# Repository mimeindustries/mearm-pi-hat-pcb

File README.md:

## MeArm Raspberry Pi HAT PCB

This repository contains the KiCAD project for the MeArm Raspberry Pi HAT

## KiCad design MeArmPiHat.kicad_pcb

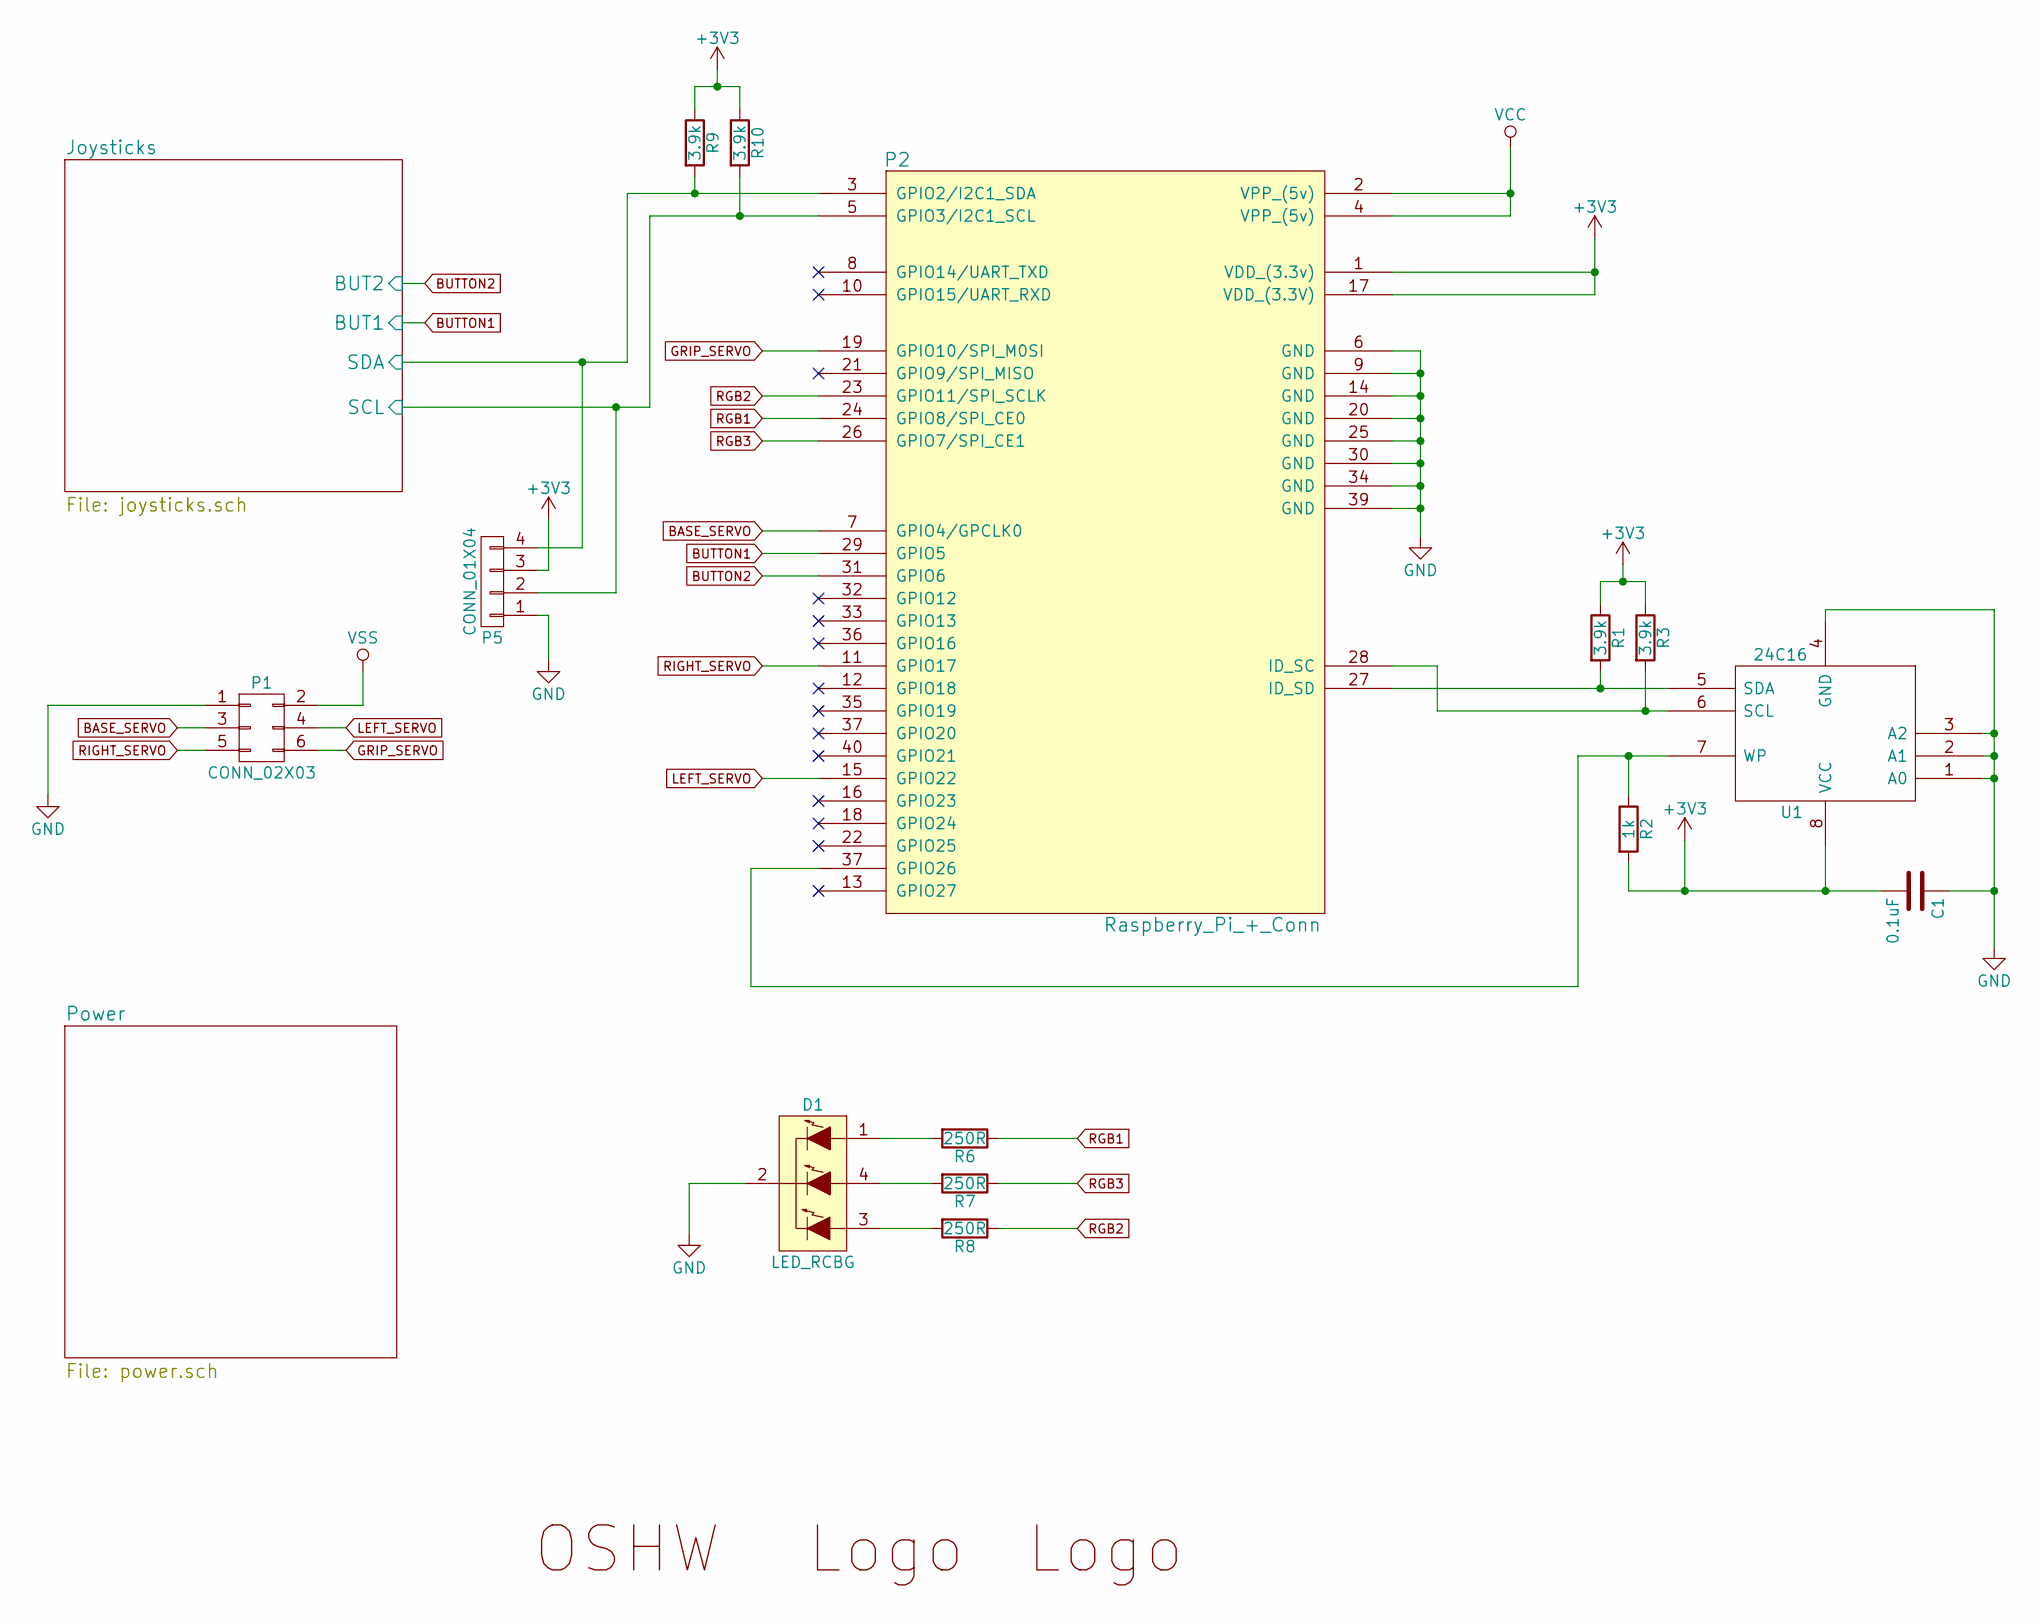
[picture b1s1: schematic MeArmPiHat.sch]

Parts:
ART1: OSHW-LOGO; OSHW_LOGO
ART2: LOGO; MEARM_LOGO_NEW_LARGE
ART3: LOGO; MIME_LOGO
C1: 0.1uF; C_0603
D1: LED_RCBG; LED-RGB-5MM_Common_Cathode
P1: CONN_02X03; Pin_Header_Straight_2x03
P2: Raspberry_Pi_+_Conn; 02x40-SMD-Socket-Flipped; Manfr. Part Number (MFP) REF-182665-01
P5: CONN_01X04; Pin_Header_Angled_1x04
R1, R3, R9, R10: 3.9k; R_0603
R2: 1k; R_0603
R6, R7, R8: 250R; R_0603
U1: 24C16; SOIC-8-N; Manfr. Part Number (MFP) CAT24C32WI

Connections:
+3V3: C1.2, P2.1 (VDD_(3.3v)), P2.17 (VDD_(3.3V)), P5.3, R1.1, R2.2, R3.1, R9.1, R10.1, U1.8 (VCC); also elsewhere on the board
/Joysticks/SCL: P2.5 (GPIO3/I2C1_SCL), P5.2, R10.2; also elsewhere on the board
/Joysticks/SDA: P2.3 (GPIO2/I2C1_SDA), P5.4, R9.2; also elsewhere on the board
BASE_SERVO: P1.3, P2.7 (GPIO4/GPCLK0)
BUTTON1: P2.29 (GPIO5); also elsewhere on the board
BUTTON2: P2.31 (GPIO6); also elsewhere on the board
GND: C1.1, D1.2 (COMMON_CATHODE), P1.1, P2.6 (GND), P2.9 (GND), P2.14 (GND), P2.20 (GND), P2.25 (GND), P2.30 (GND), P2.34 (GND), P2.39 (GND), P5.1, U1.1 (A0), U1.2 (A1), U1.3 (A2), U1.4 (GND); also elsewhere on the board
GRIP_SERVO: P1.6, P2.19 (GPIO10/SPI_M0SI)
LEFT_SERVO: P1.4, P2.15 (GPIO22)
unnamed: D1.1 (RED_ANODE), R6.2
unnamed: D1.3 (BLUE_ANODE), R8.2
unnamed: D1.4 (GREEN_ANODE), R7.2
unnamed: P2.27 (ID_SD), R1.2, U1.5 (SDA)
unnamed: P2.28 (ID_SC), R3.2, U1.6 (SCL)
unnamed: P2.37 (GPIO20), R2.1, U1.7 (WP)
RGB1: P2.24 (GPIO8/SPI_CE0), R6.1
RGB2: P2.23 (GPIO11/SPI_SCLK), R8.1
RGB3: P2.26 (GPIO7/SPI_CE1), R7.1
RIGHT_SERVO: P1.5, P2.11 (GPIO17)
VCC: P2.2 (VPP_(5v)), P2.4 (VPP_(5v)); also elsewhere on the board
VSS: P1.2; also elsewhere on the board

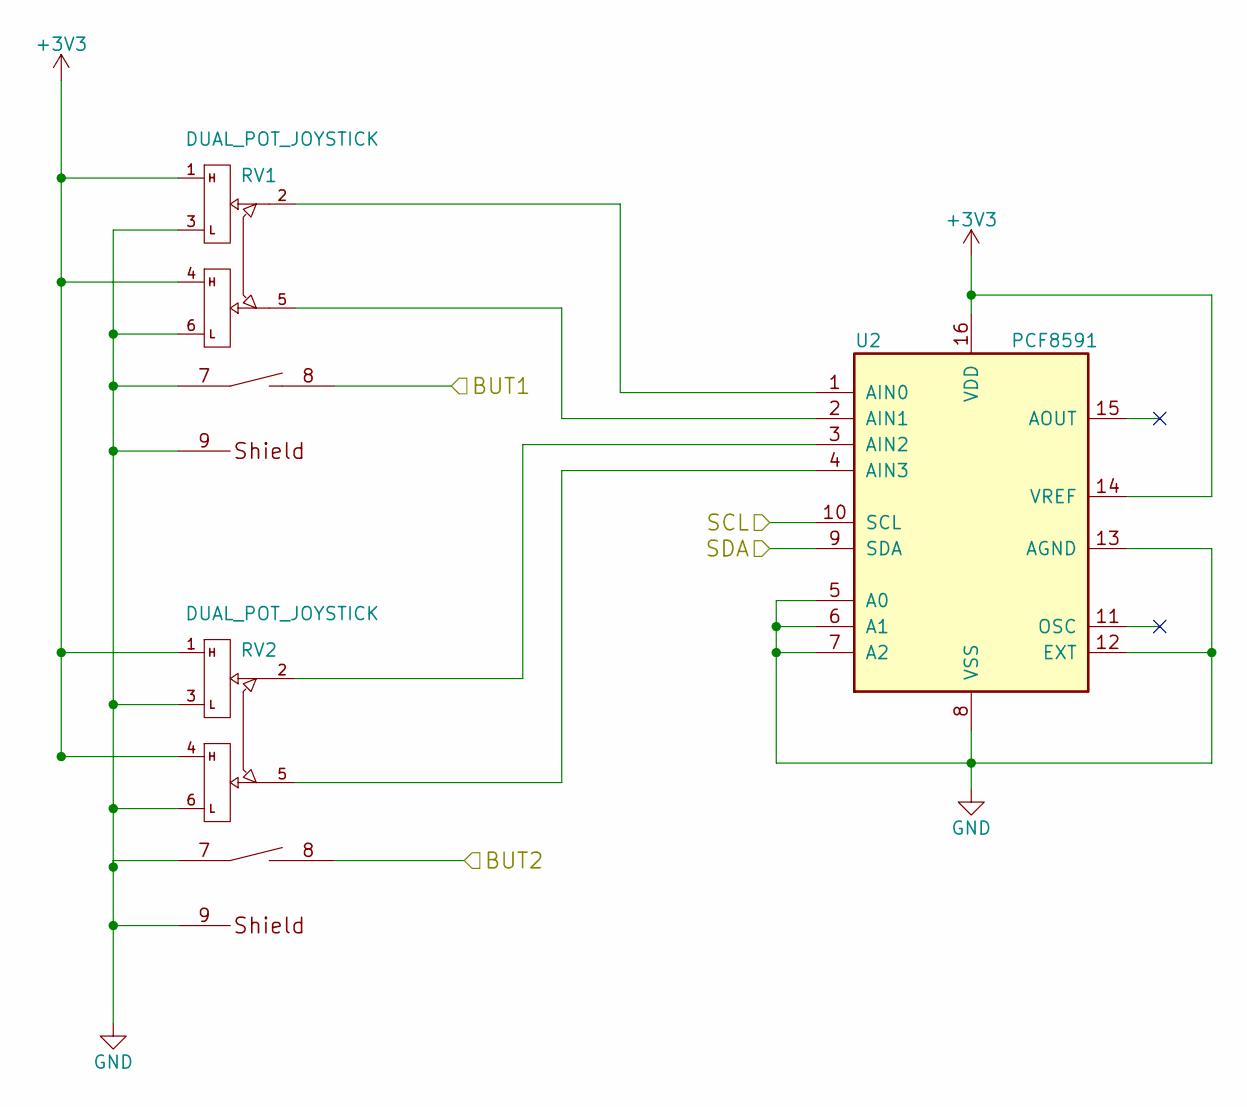
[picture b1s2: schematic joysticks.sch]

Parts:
RV1, RV2: DUAL_POT_JOYSTICK; JOYSTICK
U2: PCF8591; SO-16-W; Manfr. Part Number (MFP) PCF8591T

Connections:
+3V3: RV1.1, RV1.4, RV2.1, RV2.4, U2.14 (VREF), U2.16 (VDD); also elsewhere on the board
/Joysticks/SCL: U2.10 (SCL); also elsewhere on the board
/Joysticks/SDA: U2.9 (SDA); also elsewhere on the board
BUTTON1: RV1.8; also elsewhere on the board
BUTTON2: RV2.8; also elsewhere on the board
GND: RV1.3, RV1.6, RV1.7, RV1.9 (Shield), RV2.3, RV2.6, RV2.7, RV2.9 (Shield), U2.5 (A0), U2.6 (A1), U2.7 (A2), U2.8 (VSS), U2.12 (EXT), U2.13 (AGND); also elsewhere on the board
unnamed: RV1.2, U2.1 (AIN0)
unnamed: RV1.5, U2.2 (AIN1)
unnamed: RV2.2, U2.3 (AIN2)
unnamed: RV2.5, U2.4 (AIN3)

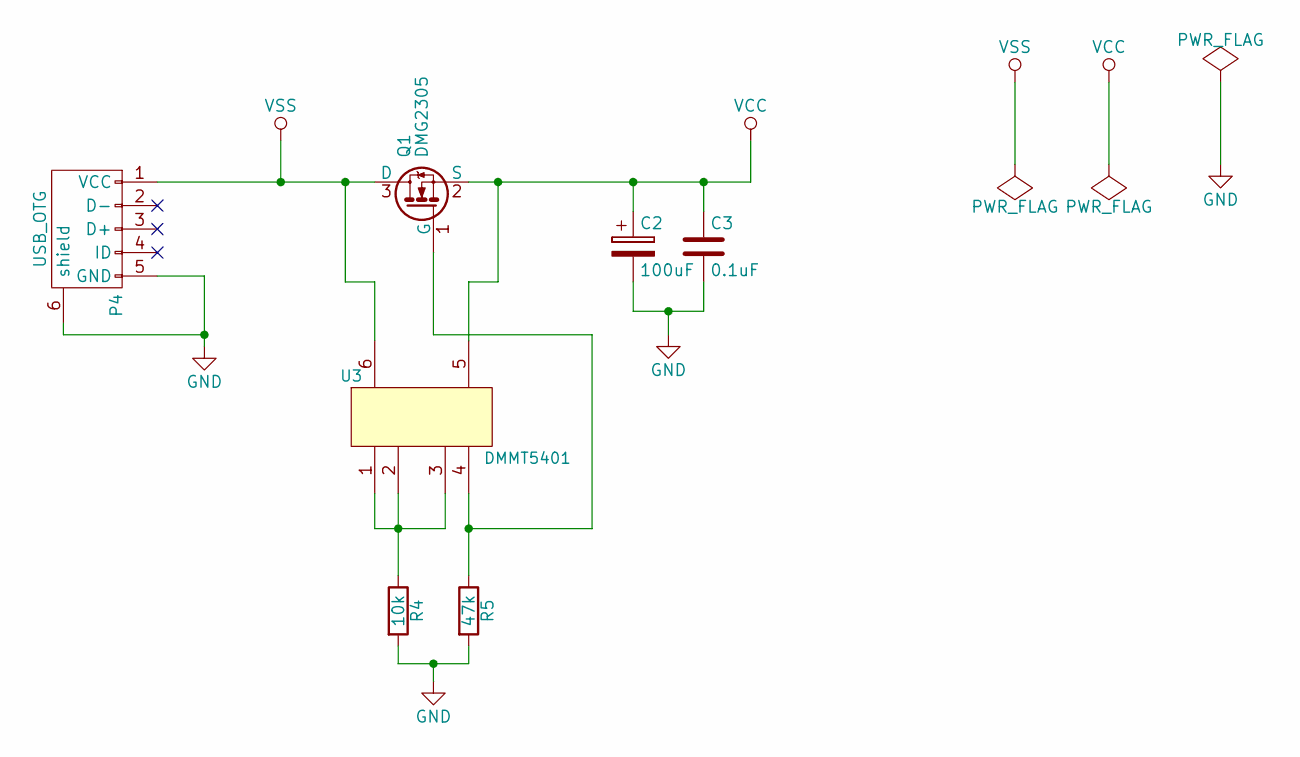
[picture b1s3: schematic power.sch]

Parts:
C2: 100uF; TantalC_SizeB_EIA-3528_Reflow
C3: 0.1uF; C_0603
P4: USB_OTG; AMPHENOL_MICRO_USB_REVERSED; Manfr. Part Number (MFP) 10103592-0001LF
Q1: DMG2305; SOT-23; Manfr. Part Number (MFP) DMG2305UX-7
R4: 10k; R_0603
R5: 47k; R_0603
U3: DMMT5401; SOT-23-6; Manfr. Part Number (MFP) DMMT5401-7-F

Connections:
GND: C2.2, C3.2, P4.5 (GND), P4.6 (shield), R4.2, R5.2; also elsewhere on the board
unnamed: Q1.1 (G), R5.1, U3.4
unnamed: R4.1, U3.1, U3.2, U3.3
VCC: C2.1, C3.1, Q1.2 (S), U3.5; also elsewhere on the board
VSS: P4.1 (VCC), Q1.3 (D), U3.6; also elsewhere on the board

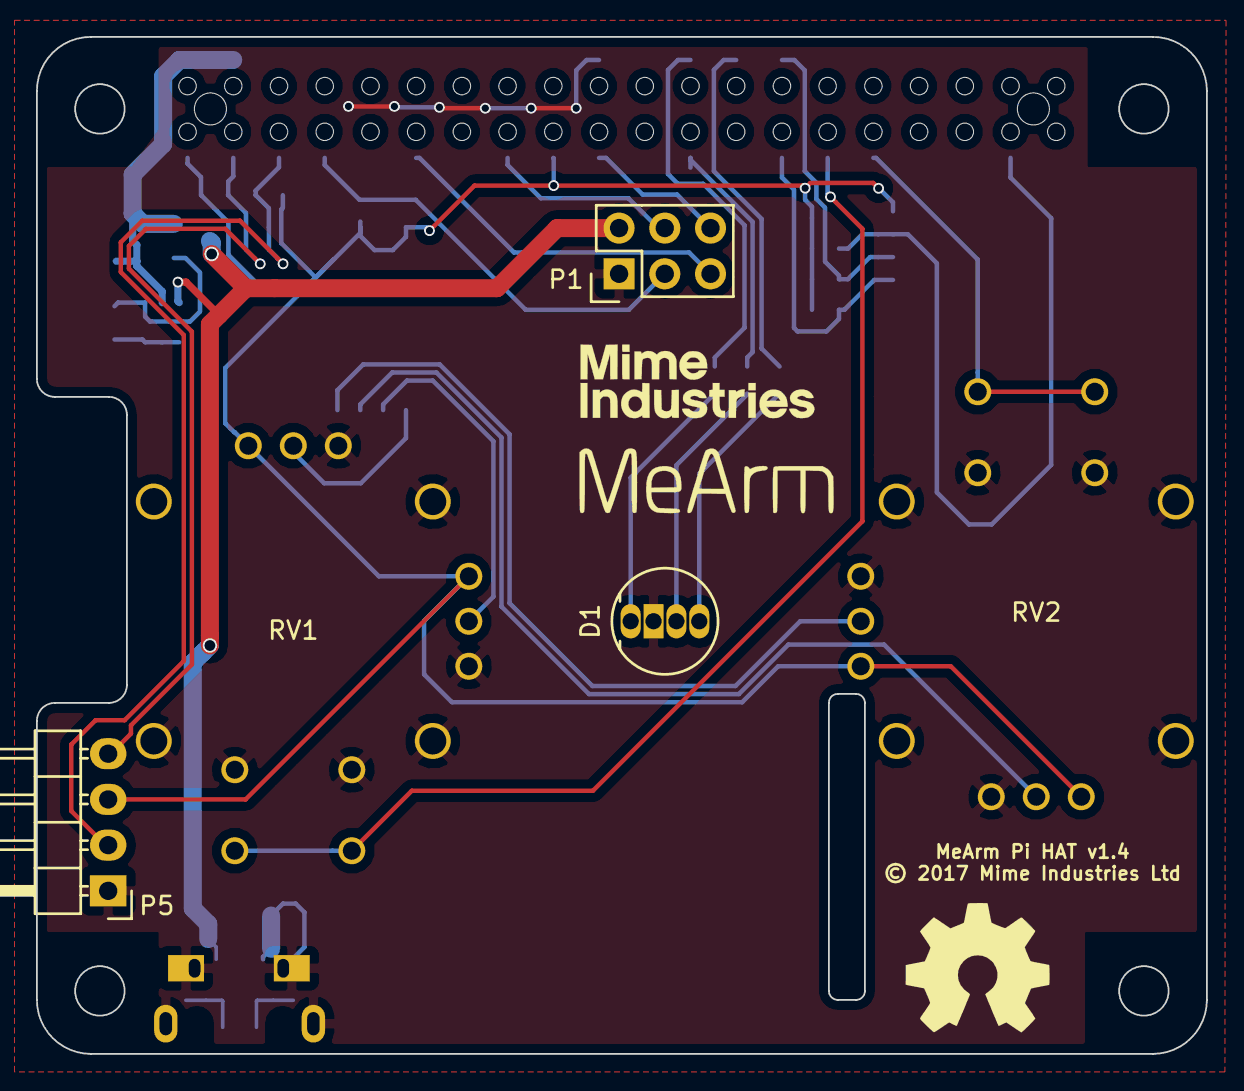
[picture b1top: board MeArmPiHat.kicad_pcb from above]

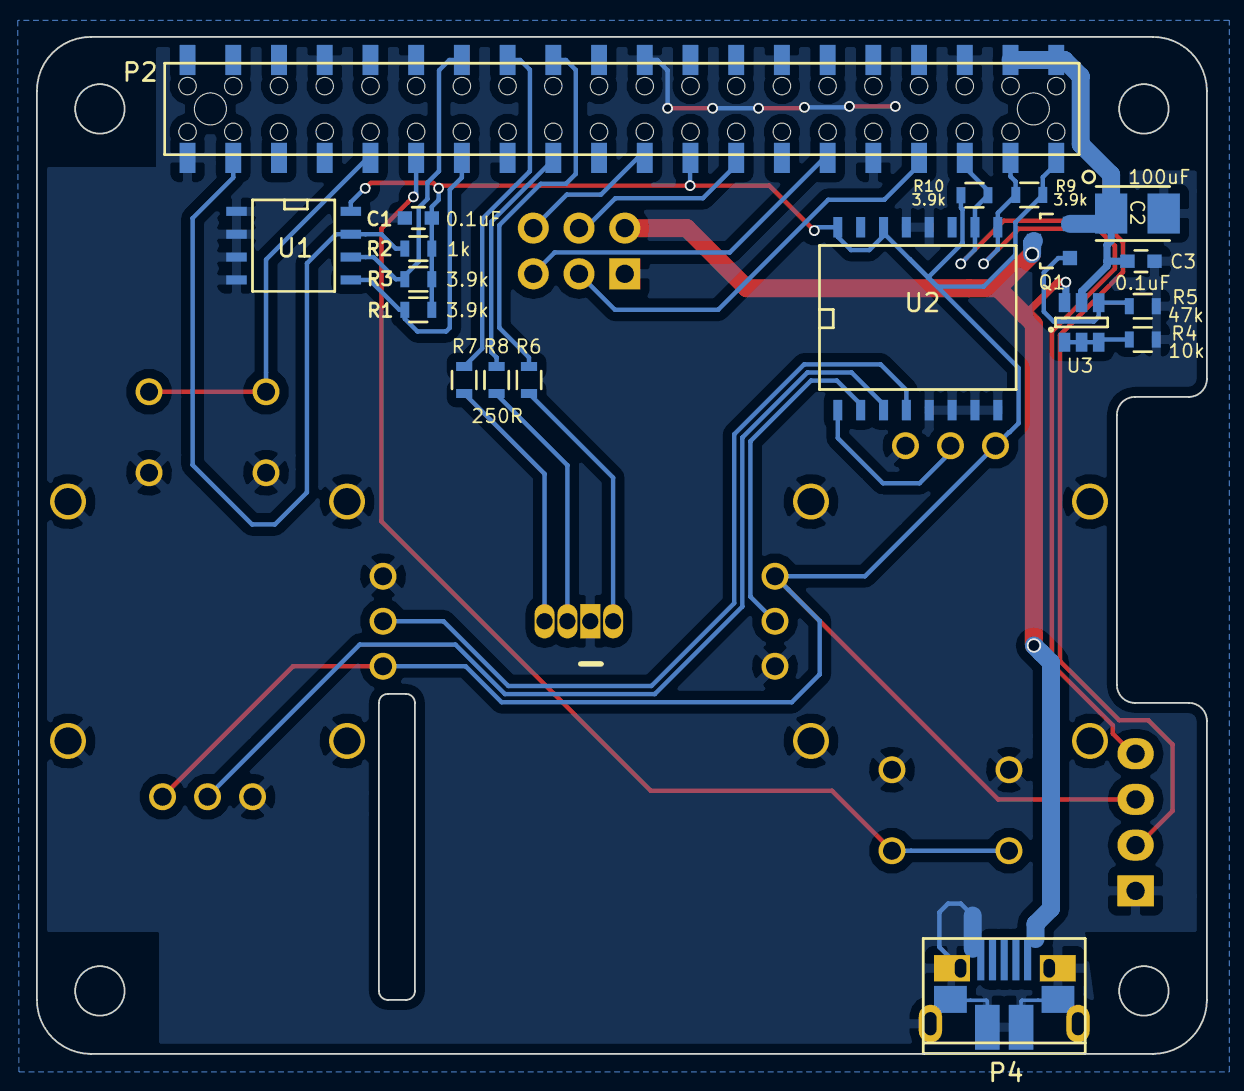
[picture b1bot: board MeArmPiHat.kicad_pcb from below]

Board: 2 copper layers, 65.0 x 56.5 mm, 27 parts (19 on the bottom side), 27 nets.

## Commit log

2017-10-23 v1.4 of the Pi HAT

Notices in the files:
MeArmPiHat.kicad_pcb:
© 2017 Mime Industries Ltd
